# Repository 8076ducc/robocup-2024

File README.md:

# ducc. Robotics: RoboCupJunior Soccer 2024

This repository contains ducc's working files and source code for the 2024 RoboCupJunior Soccer Open and Soccer Lightweight competition.

## About

ducc is a six-man team comprising Neo Hao Jun, Isaac Tan, Zhu Yunsong, Aidan Yeong, Oliver Zhao, and Ng Aaron from the Hwa Chong Robotics Club in Singapore.

## Technologies

This project was built with the following tools:

- Mechanical: Autodesk Fusion 360
- Electrical: KiCad
- Programming: PlatformIO

## Intellectual Property

### Copyright

© 2023, ducc. Robotics Competition Team.

While we have made every effort to abide by legal and ethical requirements when using works that we did not create, some may have been overlooked inadvertently. Please let us know and we will be happy to make the necessary arrangements.

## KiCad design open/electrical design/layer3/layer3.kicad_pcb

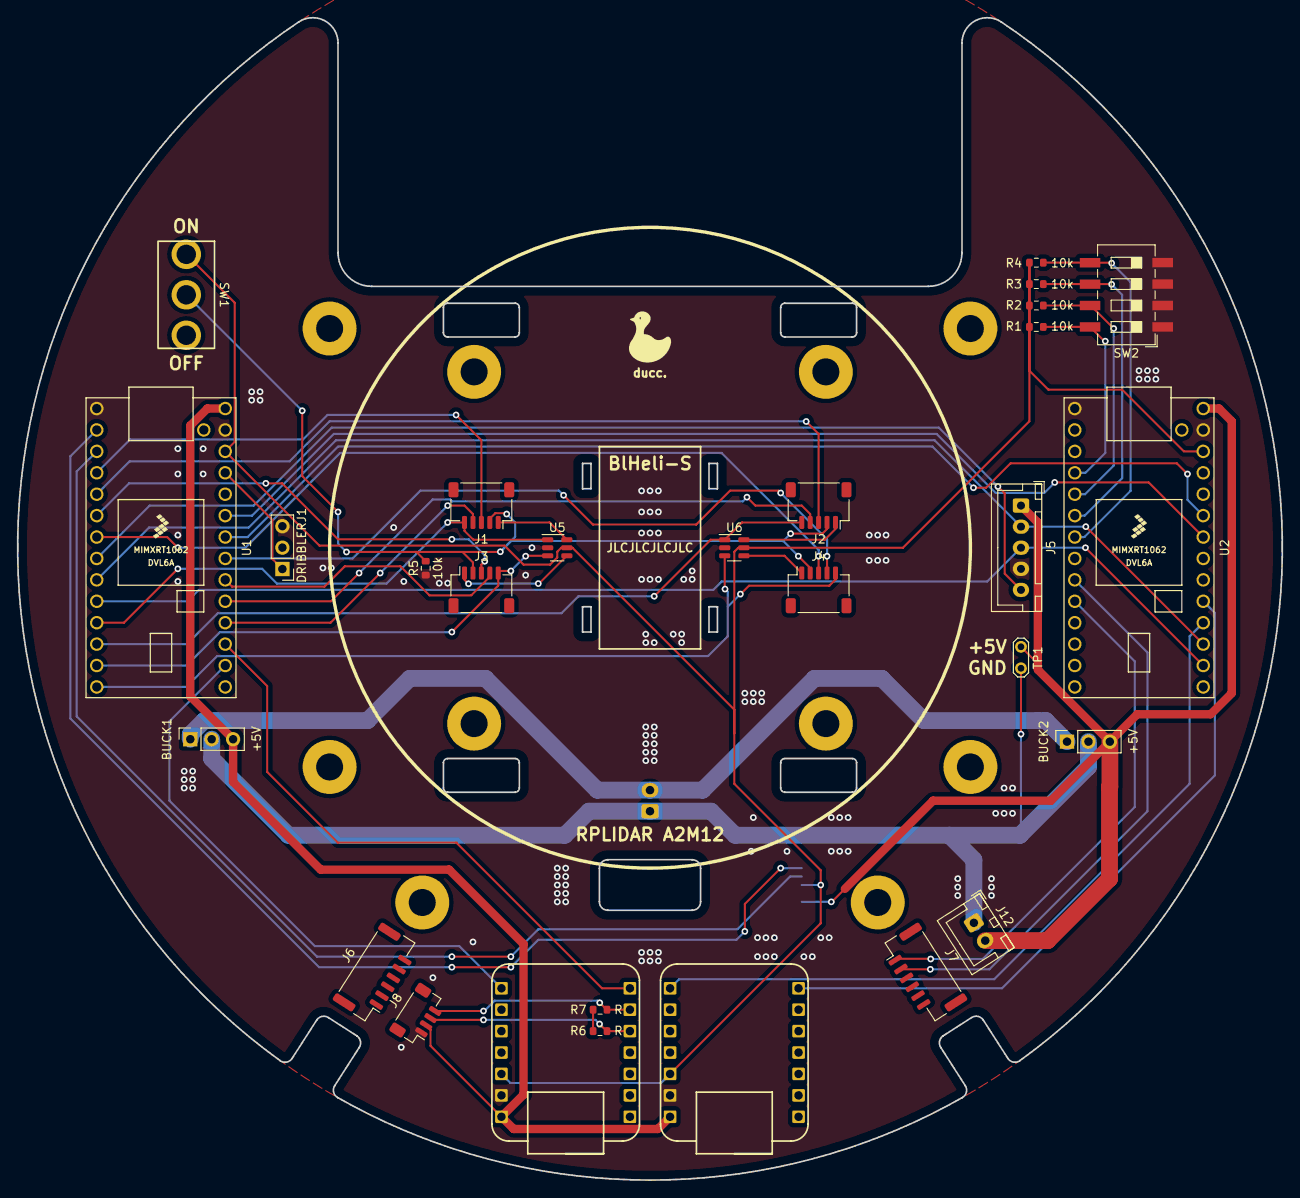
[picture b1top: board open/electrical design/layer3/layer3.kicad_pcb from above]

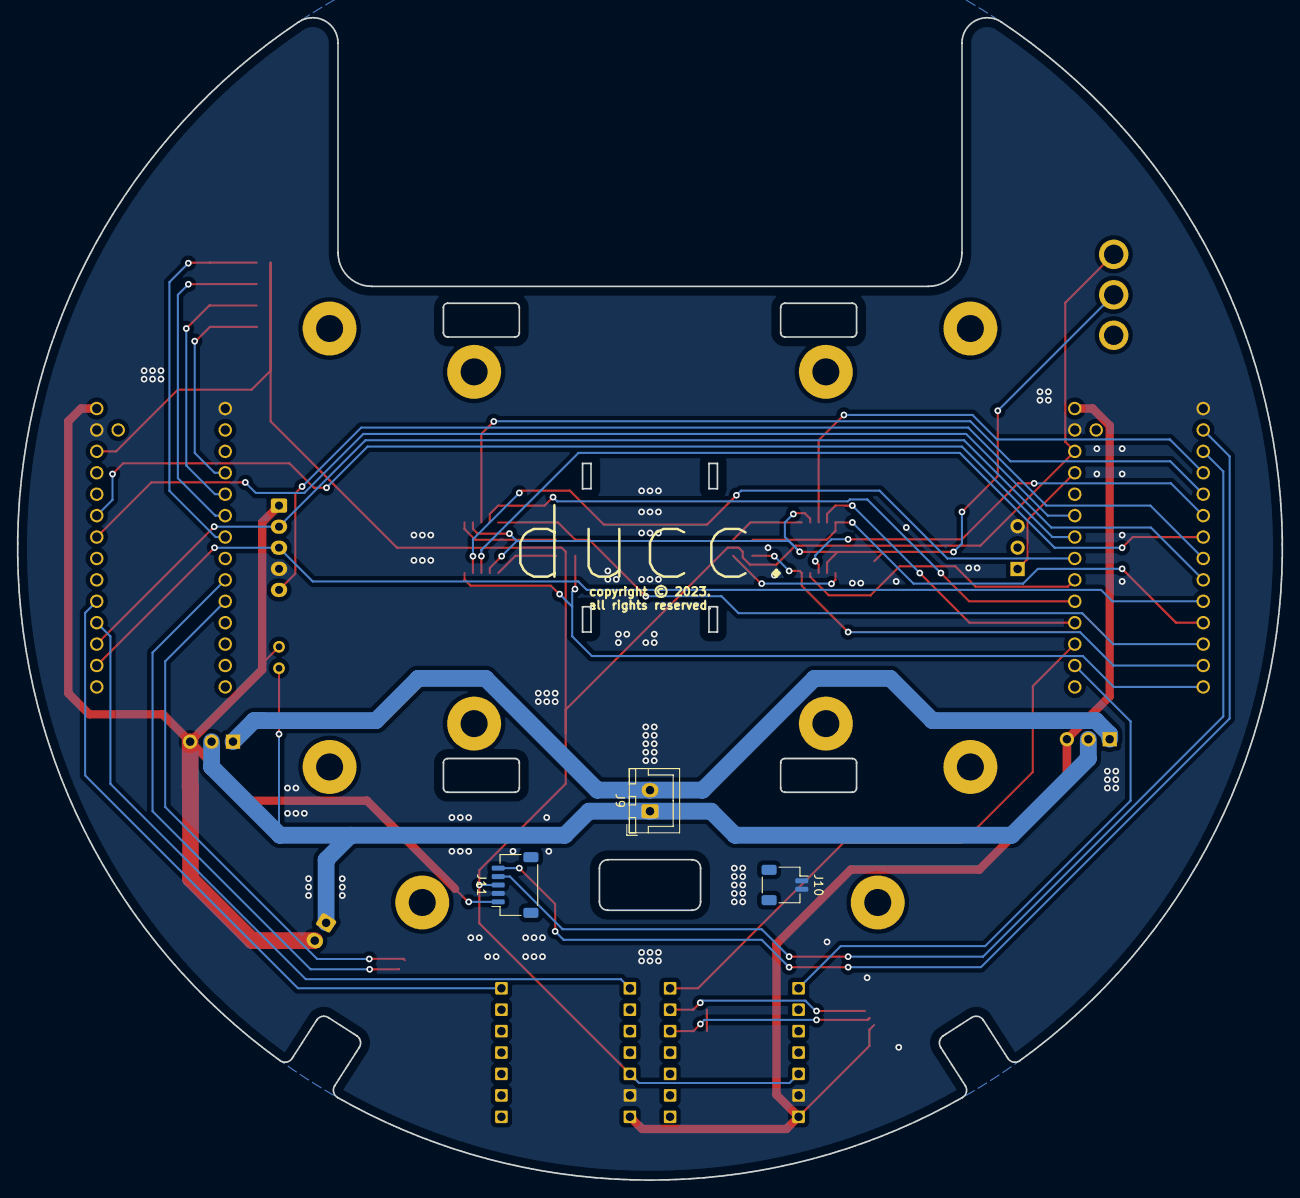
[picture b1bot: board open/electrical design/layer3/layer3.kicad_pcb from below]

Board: 2 copper layers, 150.0 x 137.9 mm, 41 parts (3 on the bottom side), 45 nets.

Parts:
BUCK1, BUCK2: +5V; TPS5430 Board
DRIBBLERJ1: Conn_01x03_Male; PinHeader_1x03_P2.54mm_Vertical
H1, H2, H3, H4, H5, H6, H7, H8, H9, H10: MountingHole; MountingHole_3.2mm_M3_Pad
J1, J2, J3, J4, J11: SH1.0 5P; JST_SH_SM05B-SRSS-TB_1x05-1MP_P1.00mm_Horizontal
J5: XH2.54 5P; JST_XH_B5B-XH-A_1x05_P2.50mm_Vertical
J6: CAMERA1; JST_GH_BM06B-GHS-TBT_1x06-1MP_P1.25mm_Vertical
J7: CAMERA2; JST_GH_BM06B-GHS-TBT_1x06-1MP_P1.25mm_Vertical
J8: COMPASS; JST_SH_BM04B-SRSS-TB_1x04-1MP_P1.00mm_Vertical
J9, J12: XH2.54 2P; JST_XH_B2B-XH-A_1x02_P2.50mm_Vertical
J10: SH1.0 2P; JST_SH_SM02B-SRSS-TB_1x02-1MP_P1.00mm_Horizontal
R1, R2, R3, R4, R5: 10k; R_0603_1608Metric
R6, R7: R; R_0603_1608Metric
SW1: SW_SPDT; SWITCH_SPDT_PTH_12.7X6.7MM
SW2: SW_DIP_x04; SW_DIP_SPSTx04_Slide_6.7x11.72mm_W8.61mm_P2.54mm_LowProfile
TP1: TestPoint_2Pole; TestPoint_2Pads_Pitch2.54mm_Drill0.8mm
U1, U2: TEENSY 4.0; Teensy40
U3, U4: MOUDLE-SEEEDUINO-XIAO-ESP32C3; xiao-esp32c3
U5, U6: 74LVC2G04; SOT-23-6

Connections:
+3V3: J11.3, R1.1, R2.1, R3.1, R4.1, SW1.1 (A), U1.3.3V_2, U2.3.3V_2, U3.12 (3V3), U4.12 (3V3), U5.5 (VCC), U6.5 (VCC)
+5V: BUCK1.3, BUCK2.3, J5.1, J8.2, J11.1, J12.2, TP1.1, U1.VIN, U2.VIN, U3.14 (5V), U4.14 (5V)
+12V: BUCK1.1, BUCK2.1, J9.2
/BTRX: U2.17, U4.7 (PB08_A6_D6_TX)
/BTTX: U2.16, U4.8 (PB09_A7_D7_RX)
/CAM1RX: J6.1, U2.1
/CAM1TX: J6.2, U2.0
/CAM2RX: J7.1, U2.8
/CAM2TX: J7.2, U2.7
/DRIBBLERPWM: DRIBBLERJ1.1, U1.23
/EN: J1.2, J2.2, J3.2, J4.2, R5.2, SW1.2 (B)
/IMURX: U1.14, U3.8 (PB09_A7_D7_RX)
/IMUSCL: J8.4, R7.1, U3.6 (PA9_A5_D5_SCL)
/IMUSDA: J8.3, R6.1, U3.5 (PA8_A4_D4_SDA)
/IMUTX: U1.15, U3.7 (PB08_A6_D6_TX)
/L1RX: J11.4, U1.1
/L1TX: J11.5, U1.0
/LIDARPWM: J5.5, U1.6
/LIDARRX: J5.3, U1.8, U2.14
/LIDARTX: J5.2, U1.7, U2.15
/M1CS: J1.4, U1.16
/M1INA: J1.5, U1.9, U5.1
/M1INB: J1.1, U5.6
/M1PWM: J1.3, U1.2
/M2CS: J2.4, U1.17
/M2INA: J2.5, U1.10, U6.1
/M2INB: J2.1, U6.6
/M2PWM: J2.3, U1.3
/M3CS: J3.4, U1.18
/M3INA: J3.5, U1.11, U5.3
/M3INB: J3.1, U5.4
/M3PWM: J3.3, U1.4
/M4CS: J4.4, U1.19
/M4INA: J4.5, U1.12, U6.3
/M4INB: J4.1, U6.4
/M4PWM: J4.3, U1.5
/RX: U1.20, U2.21
/STRAT1: R1.2, SW2.8, U2.2
/STRAT2: R2.2, SW2.7, U2.3
/STRAT3: R3.2, SW2.6, U2.4
/STRAT4: R4.2, SW2.5, U2.5
/TX: U1.21, U2.20
GNDD: DRIBBLERJ1.3, J5.4, J8.1, J10.1, J10.2, J11.2, R5.1, SW2.1, SW2.2, SW2.3, SW2.4, U1.G1, U1.G3, U2.G1, U2.G3, U3.13 (GND), U4.13 (GND), U5.2 (GND), U6.2 (GND)
GNDPWR: BUCK1.2, BUCK2.2, J9.1, J12.1, TP1.2
unnamed: R6.2, R7.2

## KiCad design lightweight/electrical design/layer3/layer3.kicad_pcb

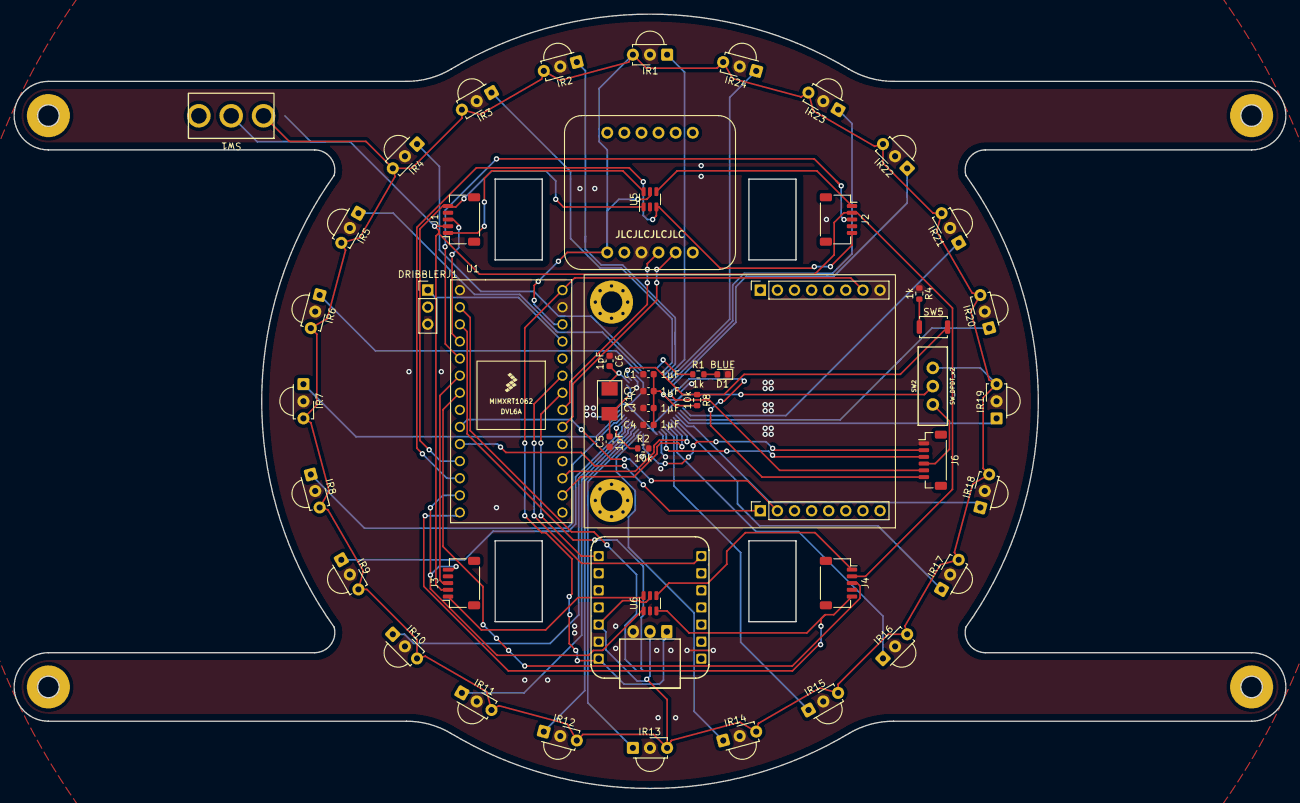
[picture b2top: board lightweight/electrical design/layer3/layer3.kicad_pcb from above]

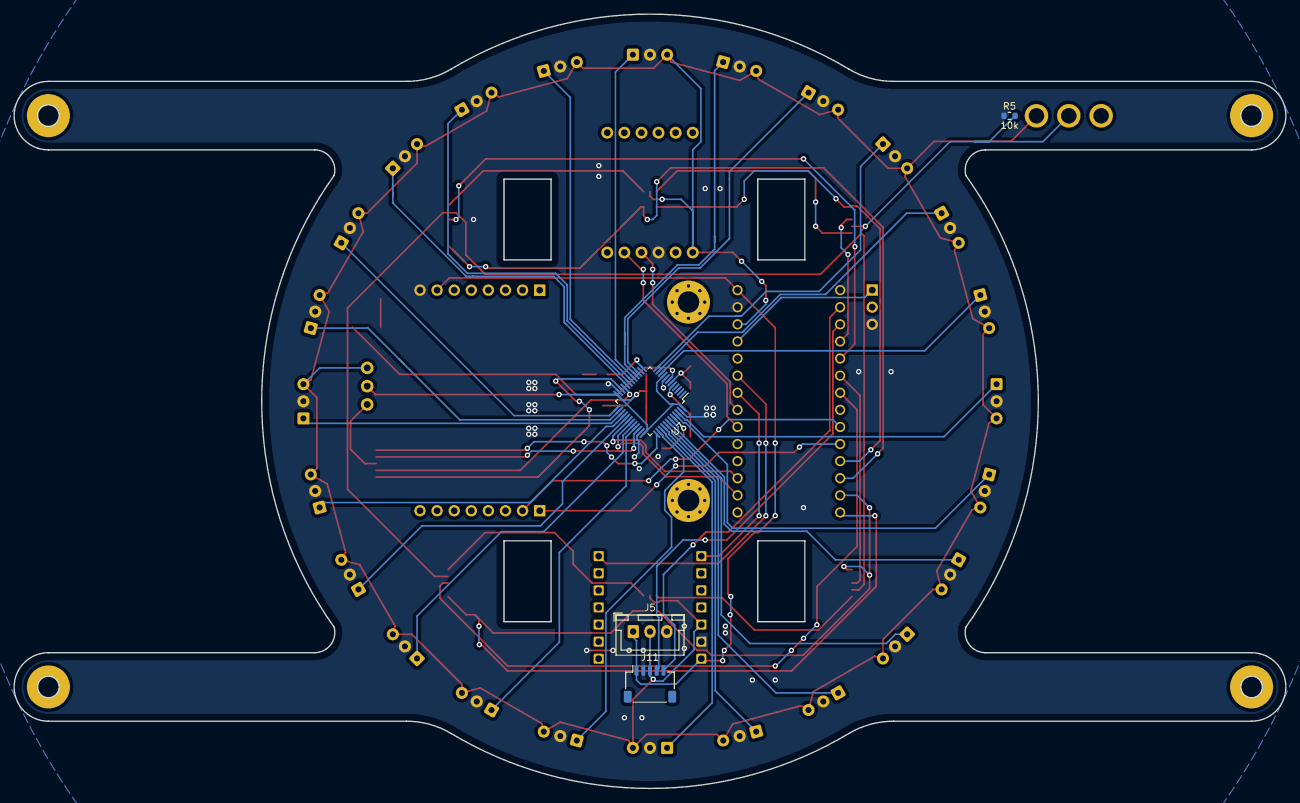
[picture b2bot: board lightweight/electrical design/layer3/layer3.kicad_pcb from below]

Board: 2 copper layers, 188.9 x 115.0 mm, 59 parts (4 on the bottom side), 64 nets.

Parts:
C1, C2, C3, C4: 1μF; C_0603_1608Metric
C5, C6: 1pF; C_0603_1608Metric
D1: BLUE; D_0603_1608Metric
DRIBBLERJ1: Conn_01x03_Male; PinHeader_1x03_P2.54mm_Vertical
H1, H2, H3, H4: MountingHole; MountingHole_3.2mm_M3_Pad
IR1, IR2, IR3, IR4, IR5, IR6, IR7, IR8, IR9, IR10, IR11, IR12, IR13, IR14, IR15, IR16, IR17, IR18, IR19, IR20, IR21, IR22, IR23, IR24: TSSP58038; Vishay_MINICAST-3Pin
J1, J2, J3, J4, J11: SH1.0 5P; JST_SH_SM05B-SRSS-TB_1x05-1MP_P1.00mm_Horizontal
J5: Conn_01x03_Pin; JST_XH_B3B-XH-A_1x03_P2.50mm_Vertical
J6: SH1.0 Female; JST_SH_BM06B-SRSS-TB_1x06-1MP_P1.00mm_Vertical
R1, R4: 1k; R_0603_1608Metric
R2, R5, R8: 10k; R_0603_1608Metric
SW1: SW_SPDT; SWITCH_SPDT_PTH_12.7X6.7MM
SW2: SW_DPDT_x2; SWITCH_SPDT_PTH_11.6X4.0MM_LOCK
SW5: SW_Push; SW_Push_SPST_NO_Alps_SKRK
U1: TEENSY 4.0; Teensy 4.0
U2: MOUDLE-SEEEDUINO-XIAO-ESP32C3; xiao-esp32c3
U3: Conn_01x16_Socket; openmv
U4: BNO085; bno085
U5, U6: 74LVC2G04; SOT-23-6
U7: STM32F103C8T6; LQFP-48_7x7mm_P0.5mm
Y1: Crystal; Crystal_SMD_5032-2Pin_5.0x3.2mm

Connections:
+3V3: IR1.3 (Vs), IR2.3 (Vs), IR3.3 (Vs), IR4.3 (Vs), IR5.3 (Vs), IR6.3 (Vs), IR7.3 (Vs), IR8.3 (Vs), IR9.3 (Vs), IR10.3 (Vs), IR11.3 (Vs), IR12.3 (Vs), IR13.3 (Vs), IR14.3 (Vs), IR15.3 (Vs), IR16.3 (Vs), IR17.3 (Vs), IR18.3 (Vs), IR19.3 (Vs), IR20.3 (Vs), IR21.3 (Vs), IR22.3 (Vs), IR23.3 (Vs), IR24.3 (Vs), J5.2, J11.3, SW1.1 (A), SW2.1 (A), U1.3.3V_2, U2.12 (3V3), U4.JP1_1 (VIN), U5.5 (VCC), U6.5 (VCC)
+5V: J5.1, J11.1, U1.VIN, U2.14 (5V), U3.10
/BTRX: U1.21, U2.7 (PB08_A6_D6_TX)
/BTTX: U1.20, U2.8 (PB09_A7_D7_RX)
/CAMRX: U1.8, U3.1
/CAMTX: U1.7, U3.2
/DRIBBLERPWM: DRIBBLERJ1.1, U1.23
/EN: J1.2, J2.2, J3.2, J4.2, R5.2, SW1.2 (B)
/IMUSCL: U1.19, U4.JP1_4 (SCL)
/IMUSDA: U1.18, U4.JP1_5 (SDA)
/L1RX: J11.4, U1.1
/L1TX: J11.5, U1.0
/M1INA: J1.5, U1.9, U5.1
/M1INB: J1.1, U5.6
/M1PWM: J1.3, U1.2
/M2INA: J2.5, U1.10, U5.3
/M2INB: J2.1, U5.4
/M2PWM: J2.3, U1.3
/M3INA: J3.5, U1.11, U6.1
/M3INB: J3.1, U6.6
/M3PWM: J3.3, U1.4
/M4INA: J4.5, U1.12, U6.3
/M4INB: J4.1, U6.4
/M4PWM: J4.3, U1.5
/ir/DEBUGRX: J6.6, U7.22 (PB11)
/ir/DEBUGTX: J6.5, U7.21 (PB10)
/ir/IR1: IR1.1 (OUT), U7.17 (PA7)
/ir/IR2: IR2.1 (OUT), U7.16 (PA6)
/ir/IR3: IR3.1 (OUT), U7.15 (PA5)
/ir/IR4: IR4.1 (OUT), U7.12 (PA2)
/ir/IR5: IR5.1 (OUT), U7.11 (PA1)
/ir/IR6: IR6.1 (OUT), U7.10 (PA0)
/ir/IR7: IR7.1 (OUT), U7.46 (PB9)
/ir/IR8: IR8.1 (OUT), U7.45 (PB8)
/ir/IR9: IR9.1 (OUT), U7.43 (PB7)
/ir/IR10: IR10.1 (OUT), U7.42 (PB6)
/ir/IR11: IR11.1 (OUT), U7.41 (PB5)
/ir/IR12: IR12.1 (OUT), U7.40 (PB4)
/ir/IR13: IR13.1 (OUT), U7.39 (PB3)
/ir/IR14: IR14.1 (OUT), U7.38 (PA15)
/ir/IR15: IR15.1 (OUT), U7.33 (PA12)
/ir/IR16: IR16.1 (OUT), U7.32 (PA11)
/ir/IR17: IR17.1 (OUT), U7.29 (PA8)
/ir/IR18: IR18.1 (OUT), U7.28 (PB15)
/ir/IR19: IR19.1 (OUT), U7.27 (PB14)
/ir/IR20: IR20.1 (OUT), U7.26 (PB13)
/ir/IR21: IR21.1 (OUT), U7.25 (PB12)
/ir/IR22: IR22.1 (OUT), U7.20 (PB2)
/ir/IR23: IR23.1 (OUT), U7.19 (PB1)
/ir/IR24: IR24.1 (OUT), U7.18 (PB0)
/ir/MCU3V3: C1.2, C2.2, C3.2, C4.2, R8.2, SW2.2 (B), U7.9 (VDDA), U7.24 (VDD), U7.36 (VDD), U7.48 (VDD)
/ir/OSCIN: C5.2, U7.5 (PD0), Y1.2
/ir/OSCOUT: C6.2, U7.6 (PD1), Y1.1
/ir/PROG3V3: J6.4, SW2.3 (C)
/ir/RESET: R8.1, SW5.2, U7.7 (NRST)
/ir/SWDCLOCK: J6.2, U7.37 (PA14)
/ir/SWDIO: J6.3, U7.34 (PA13)
GND: C1.1, C2.1, C3.1, C4.1, C5.1, C6.1, D1.1 (K), DRIBBLERJ1.3, IR1.2 (GND), IR2.2 (GND), IR3.2 (GND), IR4.2 (GND), IR5.2 (GND), IR6.2 (GND), IR7.2 (GND), IR8.2 (GND), IR9.2 (GND), IR10.2 (GND), IR11.2 (GND), IR12.2 (GND), IR13.2 (GND), IR14.2 (GND), IR15.2 (GND), IR16.2 (GND), IR17.2 (GND), IR18.2 (GND), IR19.2 (GND), IR20.2 (GND), IR21.2 (GND), IR22.2 (GND), IR23.2 (GND), IR24.2 (GND), J5.3, J6.1, J11.2, R2.2, R4.1, R5.1, U1.G1, U1.G3, U2.13 (GND), U3.9, U4.JP1_3 (GND), U5.2 (GND), U6.2 (GND), U7.8 (VSSA), U7.23 (VSS), U7.35 (VSS), U7.47 (VSS)
IRRX: U1.14, U7.31 (PA10)
IRTX: U1.15, U7.30 (PA9)
unnamed: D1.2 (A), R1.2
unnamed: R4.2, SW5.1
unnamed: R2.1, U7.44 (BOOT0)
unnamed: R1.1, U7.13 (PA3)

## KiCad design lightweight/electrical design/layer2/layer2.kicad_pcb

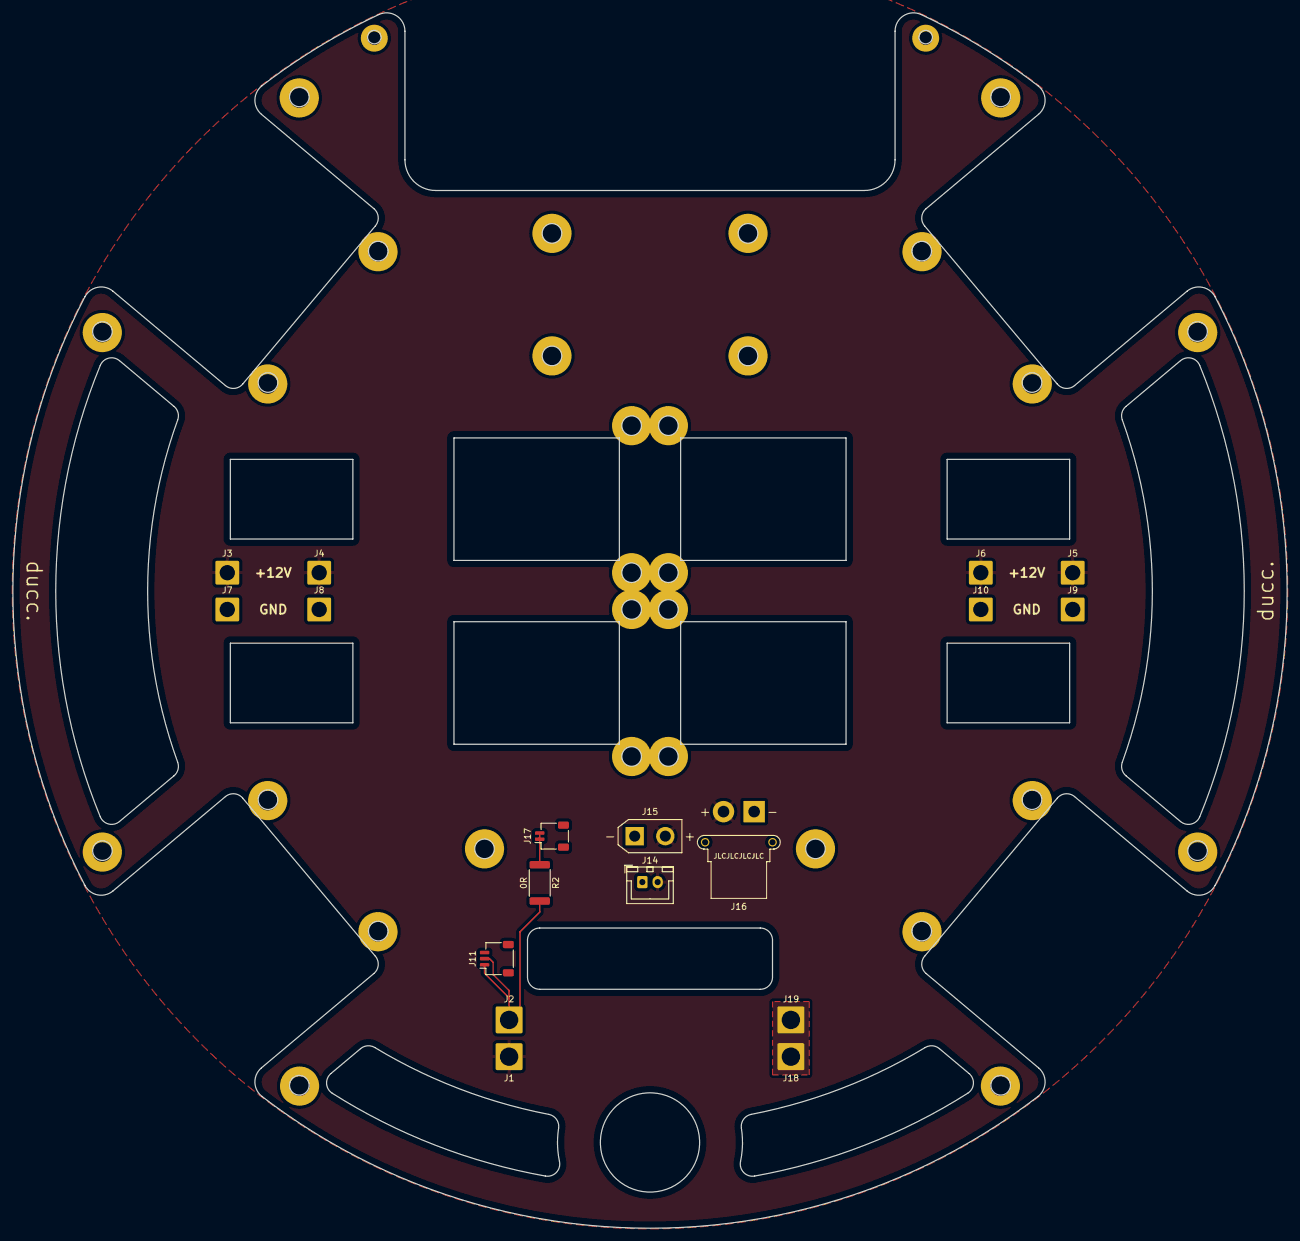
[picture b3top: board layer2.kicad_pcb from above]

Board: 2 copper layers, 208.0 x 198.4 mm, 50 parts (0 on the bottom side), 4 nets.

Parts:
H1, H2, H3, H4, H5, H6, H7, H8, H9, H10, H11, H12, H13, H14, H15, H16, H17, H18, H19, H20, H21, H22, H23, H24, H25, H26, H27, H28, H29, H30: MountingHole; MountingHole_3.2mm_M3_Pad
H33, H34: MountingHole; MountingHole_2.2mm_M2_Pad
J1, J2, J18, J19: Conn_01x01_Female; SolderWire-2.5sqmm_1x01_D2.4mm_OD4.4mm
J3, J4, J5, J6, J7, J8, J9, J10: Conn_01x01_Female; SolderWire-2sqmm_1x01_D2mm_OD3.9mm
J11: SH1.0 3P; JST_SH_SM03B-SRSS-TB_1x03-1MP_P1.00mm_Horizontal
J14: XH2.54 2P; JST_XH_B2B-XH-A_1x02_P2.50mm_Vertical
J15: XT30UPB-F; AMASS_XT30UPB-F_1x02_P5.0mm_Vertical
J16: XT30PW-F; AMASS_XT30PW-F_1x02_P2.50mm_Horizontal
J17: SH1.0 2P; JST_SH_SM02B-SRSS-TB_1x02-1MP_P1.00mm_Horizontal
R2: 0R; R_2512_6332Metric

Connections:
+12V: J1.1, J3.1, J4.1, J5.1, J6.1, J14.2, J15.2, J16.2
/BATT: J18.1, J19.1
GND: J2.1, J7.1, J8.1, J9.1, J10.1, J11.1, J11.2, J14.1, J15.1, J16.1, R2.2
unnamed: J17.1, J17.2, R2.1

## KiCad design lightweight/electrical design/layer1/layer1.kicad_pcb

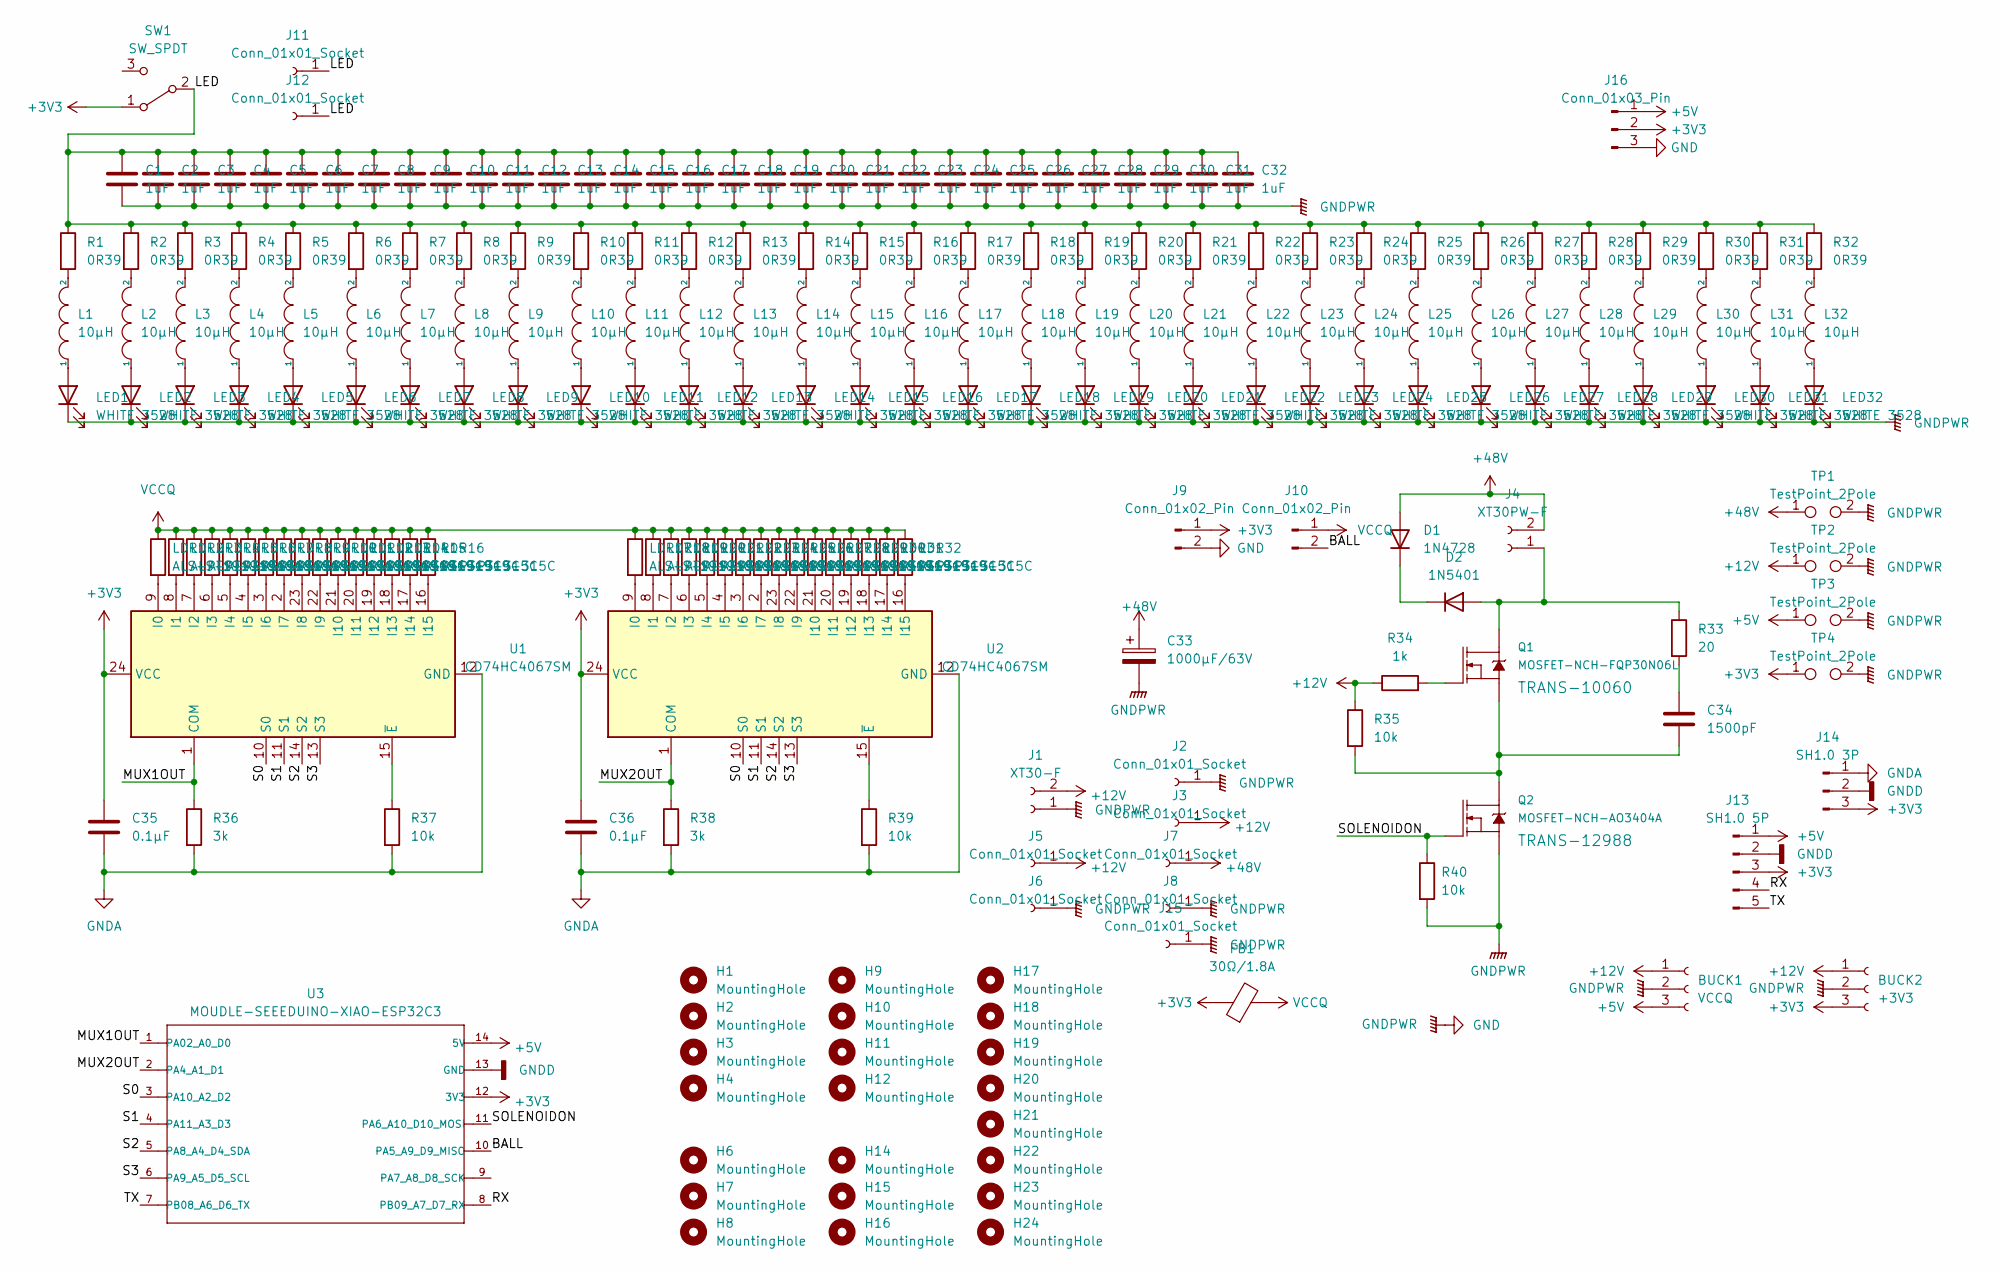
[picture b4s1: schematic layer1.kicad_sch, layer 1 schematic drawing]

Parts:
BUCK1: VCCQ; PinSocket_1x03_P2.54mm_Horizontal
BUCK2: +3V3; PinSocket_1x03_P2.54mm_Horizontal
C1, C2, C3, C4, C5, C6, C7, C8, C9, C10, C11, C12, C13, C14, C15, C16, C17, C18, C19, C20, C21, C22, C23, C24, C25, C26, C27, C28, C29, C30, C31, C32: 1uF; C_0603_1608Metric
C33: 1000µF/63V; CP_Radial_D16.0mm_P7.50mm
C34: 1500pF; C_0603_1608Metric
C35, C36: 0.1μF; C_0603_1608Metric
D1: 1N4728; D_DO-41_SOD81_P10.16mm_Horizontal
D2: 1N5401; D_DO-27_P15.24mm_Horizontal
FB1: 30Ω/1.8A; C_0603_1608Metric
H1, H2, H3, H4, H6, H7, H8, H9, H10, H11, H12, H14, H15, H16, H17, H18, H19, H20, H21, H22, H23, H24: MountingHole; MountingHole_3.2mm_M3_Pad
J1: XT30-F; AMASS_XT30UPB-F_1x02_P5.0mm_Vertical
J2, J11, J15: Conn_01x01_Socket; SolderWirePad_1x01_SMD_1x2mm
J3, J5, J6, J7, J8: Conn_01x01_Socket; SolderWirePad_1x01_SMD_5x10mm
J4: XT30PW-F; AMASS_XT30UPB-F_1x02_P5.0mm_Vertical
J9, J10: Conn_01x02_Pin; PinHeader_1x02_P2.54mm_Vertical
J12: Conn_01x01_Socket; SolderWire-0.5sqmm_1x01_D0.9mm_OD2.1mm
J13: SH1.0 5P; JST_SH_BM05B-SRSS-TB_1x05-1MP_P1.00mm_Vertical
J14: SH1.0 3P; JST_SH_BM03B-SRSS-TB_1x03-1MP_P1.00mm_Vertical
J16: Conn_01x03_Pin; JST_XH_B3B-XH-A_1x03_P2.50mm_Vertical
L1, L2, L3, L4, L5, L6, L7, L8, L9, L10, L11, L12, L13, L14, L15, L16, L17, L18, L19, L20, L21, L22, L23, L24, L25, L26, L27, L28, L29, L30, L31, L32: 10µH; L_0805_2012Metric
LDR1, LDR2, LDR3, LDR4, LDR5, LDR6, LDR7, LDR8, LDR9, LDR10, LDR11, LDR12, LDR13, LDR14, LDR15, LDR16, LDR17, LDR18, LDR19, LDR20, LDR21, LDR22, LDR23, LDR24, LDR25, LDR26, LDR27, LDR28, LDR29, LDR30, LDR31, LDR32: ALS-PT19-315C; D_0603_1608Metric
LED1, LED2, LED3, LED4, LED5, LED6, LED7, LED8, LED9, LED10, LED11, LED12, LED13, LED14, LED15, LED16, LED17, LED18, LED19, LED20, LED21, LED22, LED23, LED24, LED25, LED26, LED27, LED28, LED29, LED30, LED31, LED32: WHITE 3528; CP_EIA-3528-12_Kemet-T
Q1: MOSFET-NCH-FQP30N06L; TO-220-3_Vertical
Q2: MOSFET-NCH-AO3404A; TSOT-23
R1, R2, R3, R4, R5, R6, R7, R8, R9, R10, R11, R12, R13, R14, R15, R16, R17, R18, R19, R20, R21, R22, R23, R24, R25, R26, R27, R28, R29, R30, R31, R32: 0R39; R_0603_1608Metric
R33: 20; R_0603_1608Metric
R34: 1k; R_0603_1608Metric
R35, R37, R39, R40: 10k; R_0603_1608Metric
R36, R38: 3k; R_0603_1608Metric
SW1: SW_SPDT; SWITCH_SPDT_PTH_11.6X4.0MM
TP1, TP2, TP3, TP4: TestPoint_2Pole; TestPoint_2Pads_Pitch2.54mm_Drill0.8mm
U1, U2: CD74HC4067SM; SOIC-24W_7.5x15.4mm_P1.27mm
U3: MOUDLE-SEEEDUINO-XIAO-ESP32C3; xiao-esp32c3

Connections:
+3V3: BUCK2.3, C35.1, C36.1, FB1.1, J9.1, J13.3, J14.3, J16.2, SW1.1 (A), TP4.1, U1.24 (VCC), U2.24 (VCC), U3.12 (3V3)
+5V: BUCK1.3, J13.1, J16.1, TP3.1, U3.14 (5V)
+12V: BUCK1.1, BUCK2.1, J1.2, J3.1, J5.1, R34.1, R35.1, TP2.1
+48V: C33.1, D1.2 (A), J4.2, J7.1, TP1.1
/BALL: J10.2, U3.10 (PA5_A9_D9_MISO)
/LED: C1.1, C2.1, C3.1, C4.1, C5.1, C6.1, C7.1, C8.1, C9.1, C10.1, C11.1, C12.1, C13.1, C14.1, C15.1, C16.1, C17.1, C18.1, C19.1, C20.1, C21.1, C22.1, C23.1, C24.1, C25.1, C26.1, C27.1, C28.1, C29.1, C30.1, C31.1, C32.1, J11.1, J12.1, R1.1, R2.1, R3.1, R4.1, R5.1, R6.1, R7.1, R8.1, R9.1, R10.1, R11.1, R12.1, R13.1, R14.1, R15.1, R16.1, R17.1, R18.1, R19.1, R20.1, R21.1, R22.1, R23.1, R24.1, R25.1, R26.1, R27.1, R28.1, R29.1, R30.1, R31.1, R32.1, SW1.2 (B)
/MUX1OUT: R36.1, U1.1 (COM), U3.1 (PA02_A0_D0)
/MUX2OUT: R38.1, U2.1 (COM), U3.2 (PA4_A1_D1)
/RX: J13.4, U3.8 (PB09_A7_D7_RX)
/S0: U1.10 (S0), U2.10 (S0), U3.3 (PA10_A2_D2)
/S1: U1.11 (S1), U2.11 (S1), U3.4 (PA11_A3_D3)
/S2: U1.14 (S2), U2.14 (S2), U3.5 (PA8_A4_D4_SDA)
/S3: U1.13 (S3), U2.13 (S3), U3.6 (PA9_A5_D5_SCL)
/SOLENOIDON: Q2.1 (G), R40.1, U3.11 (PA6_A10_D10_MOSI)
/TX: J13.5, U3.7 (PB08_A6_D6_TX)
GND: BUCK1.2, BUCK2.2, C1.2, C2.2, C3.2, C4.2, C5.2, C6.2, C7.2, C8.2, C9.2, C10.2, C11.2, C12.2, C13.2, C14.2, C15.2, C16.2, C17.2, C18.2, C19.2, C20.2, C21.2, C22.2, C23.2, C24.2, C25.2, C26.2, C27.2, C28.2, C29.2, C30.2, C31.2, C32.2, C33.2, J1.1, J2.1, J6.1, J8.1, J9.2, J15.1, J16.3, LED1.1 (K), LED2.1 (K), LED3.1 (K), LED4.1 (K), LED5.1 (K), LED6.1 (K), LED7.1 (K), LED8.1 (K), LED9.1 (K), LED10.1 (K), LED11.1 (K), LED12.1 (K), LED13.1 (K), LED14.1 (K), LED15.1 (K), LED16.1 (K), LED17.1 (K), LED18.1 (K), LED19.1 (K), LED20.1 (K), LED21.1 (K), LED22.1 (K), LED23.1 (K), LED24.1 (K), LED25.1 (K), LED26.1 (K), LED27.1 (K), LED28.1 (K), LED29.1 (K), LED30.1 (K), LED31.1 (K), LED32.1 (K), Q2.2 (S), R40.2, TP1.2, TP2.2, TP3.2, TP4.2
GNDA: C35.2, C36.2, J14.1, R36.2, R37.2, R38.2, R39.2, U1.12 (GND), U2.12 (GND)
GNDD: J13.2, J14.2, U3.13 (GND)
unnamed: C34.1, R33.2
unnamed: D1.1 (K), D2.1 (K)
unnamed: D2.2 (A), J4.1, Q1.2 (D), R33.1
unnamed: L1.2, R1.2
unnamed: L2.2, R2.2
unnamed: L3.2, R3.2
unnamed: L4.2, R4.2
unnamed: L5.2, R5.2
unnamed: L6.2, R6.2
unnamed: L7.2, R7.2
unnamed: L8.2, R8.2
unnamed: L9.2, R9.2
unnamed: L10.2, R10.2
unnamed: L11.2, R11.2
unnamed: L12.2, R12.2
unnamed: L13.2, R13.2
unnamed: L14.2, R14.2
unnamed: L15.2, R15.2
unnamed: L16.2, R16.2
unnamed: L17.2, R17.2
unnamed: L18.2, R18.2
unnamed: L19.2, R19.2
unnamed: L20.2, R20.2
unnamed: L21.2, R21.2
unnamed: L22.2, R22.2
unnamed: L23.2, R23.2
unnamed: L24.2, R24.2
unnamed: L25.2, R25.2
unnamed: L26.2, R26.2
unnamed: L27.2, R27.2
unnamed: L28.2, R28.2
unnamed: L29.2, R29.2
unnamed: L30.2, R30.2
unnamed: L31.2, R31.2
unnamed: L32.2, R32.2
unnamed: L1.1, LED1.2 (A)
unnamed: L2.1, LED2.2 (A)
unnamed: L3.1, LED3.2 (A)
unnamed: L4.1, LED4.2 (A)
unnamed: L5.1, LED5.2 (A)
unnamed: L6.1, LED6.2 (A)
unnamed: L7.1, LED7.2 (A)
unnamed: L8.1, LED8.2 (A)
unnamed: L9.1, LED9.2 (A)
unnamed: L10.1, LED10.2 (A)
unnamed: L11.1, LED11.2 (A)
unnamed: L12.1, LED12.2 (A)
unnamed: L13.1, LED13.2 (A)
unnamed: L14.1, LED14.2 (A)
unnamed: L15.1, LED15.2 (A)
unnamed: L16.1, LED16.2 (A)
unnamed: L17.1, LED17.2 (A)
unnamed: L18.1, LED18.2 (A)
unnamed: L19.1, LED19.2 (A)
unnamed: L20.1, LED20.2 (A)
unnamed: L21.1, LED21.2 (A)
unnamed: L22.1, LED22.2 (A)
unnamed: L23.1, LED23.2 (A)
unnamed: L24.1, LED24.2 (A)
unnamed: L25.1, LED25.2 (A)
unnamed: L26.1, LED26.2 (A)
unnamed: L27.1, LED27.2 (A)
unnamed: L28.1, LED28.2 (A)
unnamed: L29.1, LED29.2 (A)
unnamed: L30.1, LED30.2 (A)
unnamed: L31.1, LED31.2 (A)
unnamed: L32.1, LED32.2 (A)
unnamed: Q1.1 (G), R34.2
unnamed: C34.2, Q1.3 (S), Q2.3 (D), R35.2
unnamed: LDR1.2, U1.9 (I0)
unnamed: LDR2.2, U1.8 (I1)
unnamed: LDR3.2, U1.7 (I2)
unnamed: LDR4.2, U1.6 (I3)
unnamed: LDR5.2, U1.5 (I4)
unnamed: LDR6.2, U1.4 (I5)
unnamed: LDR7.2, U1.3 (I6)
unnamed: LDR8.2, U1.2 (I7)
unnamed: LDR9.2, U1.23 (I8)
unnamed: LDR10.2, U1.22 (I9)
unnamed: LDR11.2, U1.21 (I10)
unnamed: LDR12.2, U1.20 (I11)
unnamed: LDR13.2, U1.19 (I12)
unnamed: LDR14.2, U1.18 (I13)
unnamed: LDR15.2, U1.17 (I14)
unnamed: LDR16.2, U1.16 (I15)
unnamed: R37.1, U1.15 (~E)
unnamed: LDR17.2, U2.9 (I0)
unnamed: LDR18.2, U2.8 (I1)
unnamed: LDR19.2, U2.7 (I2)
unnamed: LDR20.2, U2.6 (I3)
unnamed: LDR21.2, U2.5 (I4)
unnamed: LDR22.2, U2.4 (I5)
unnamed: LDR23.2, U2.3 (I6)
unnamed: LDR24.2, U2.2 (I7)
unnamed: LDR25.2, U2.23 (I8)
unnamed: LDR26.2, U2.22 (I9)
unnamed: LDR27.2, U2.21 (I10)
unnamed: LDR28.2, U2.20 (I11)
unnamed: LDR29.2, U2.19 (I12)
unnamed: LDR30.2, U2.18 (I13)
unnamed: LDR31.2, U2.17 (I14)
unnamed: LDR32.2, U2.16 (I15)
unnamed: R39.1, U2.15 (~E)
VCCQ: FB1.2, J10.1, LDR1.1, LDR2.1, LDR3.1, LDR4.1, LDR5.1, LDR6.1, LDR7.1, LDR8.1, LDR9.1, LDR10.1, LDR11.1, LDR12.1, LDR13.1, LDR14.1, LDR15.1, LDR16.1, LDR17.1, LDR18.1, LDR19.1, LDR20.1, LDR21.1, LDR22.1, LDR23.1, LDR24.1, LDR25.1, LDR26.1, LDR27.1, LDR28.1, LDR29.1, LDR30.1, LDR31.1, LDR32.1

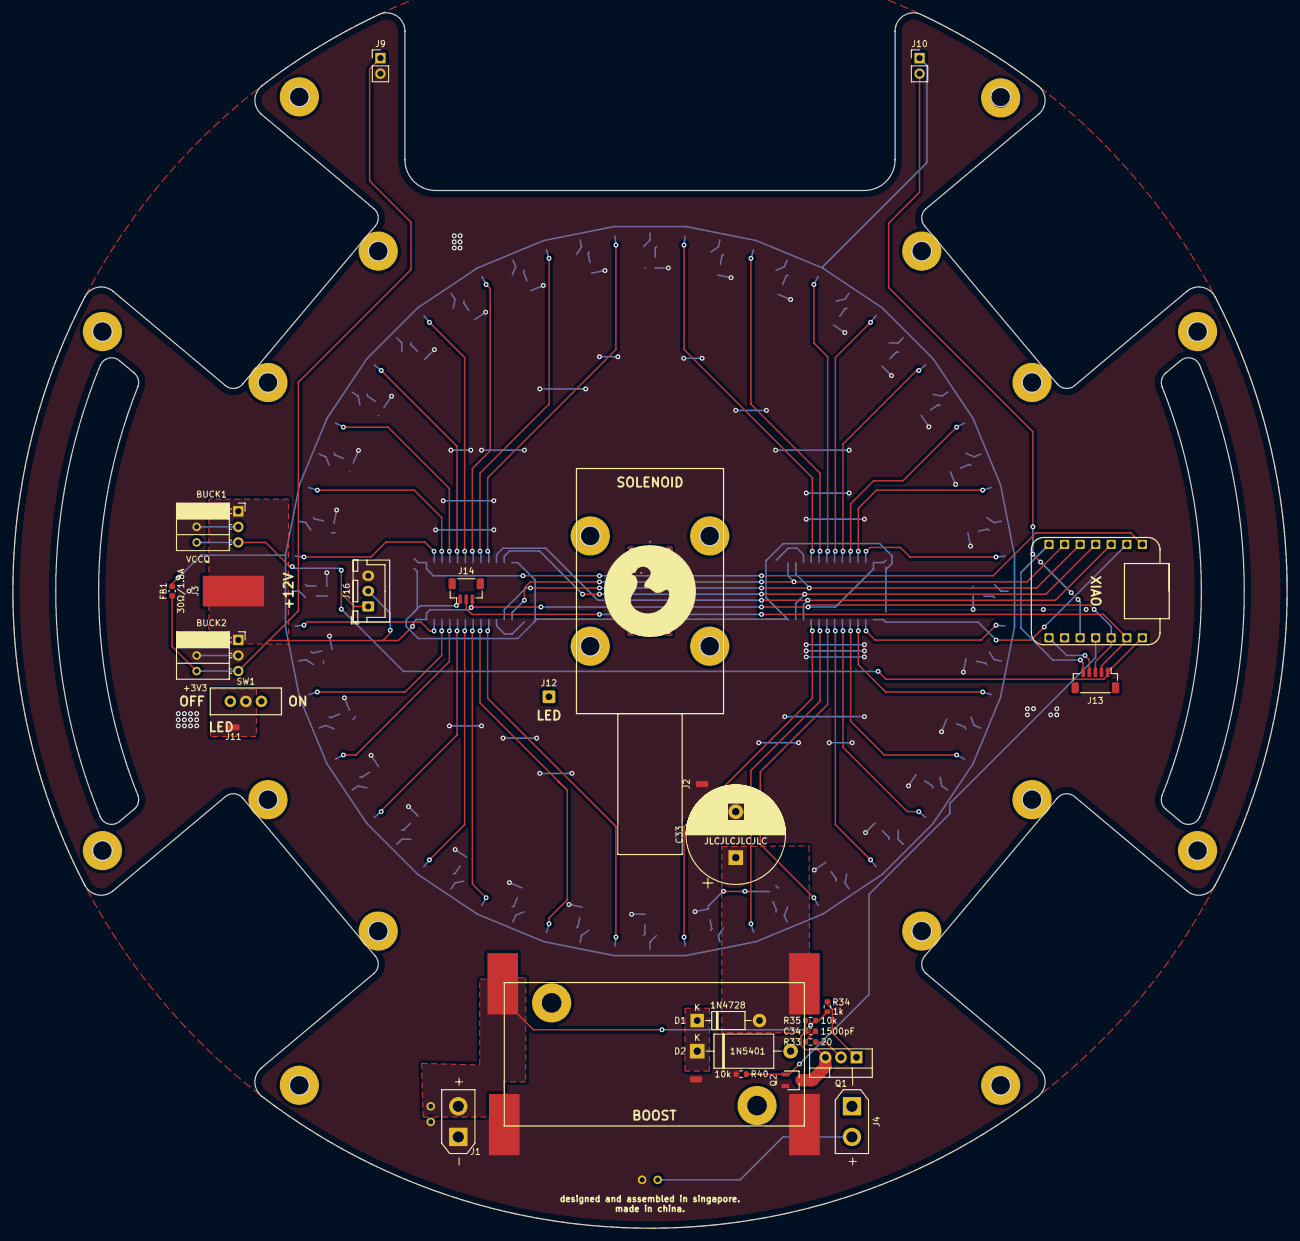
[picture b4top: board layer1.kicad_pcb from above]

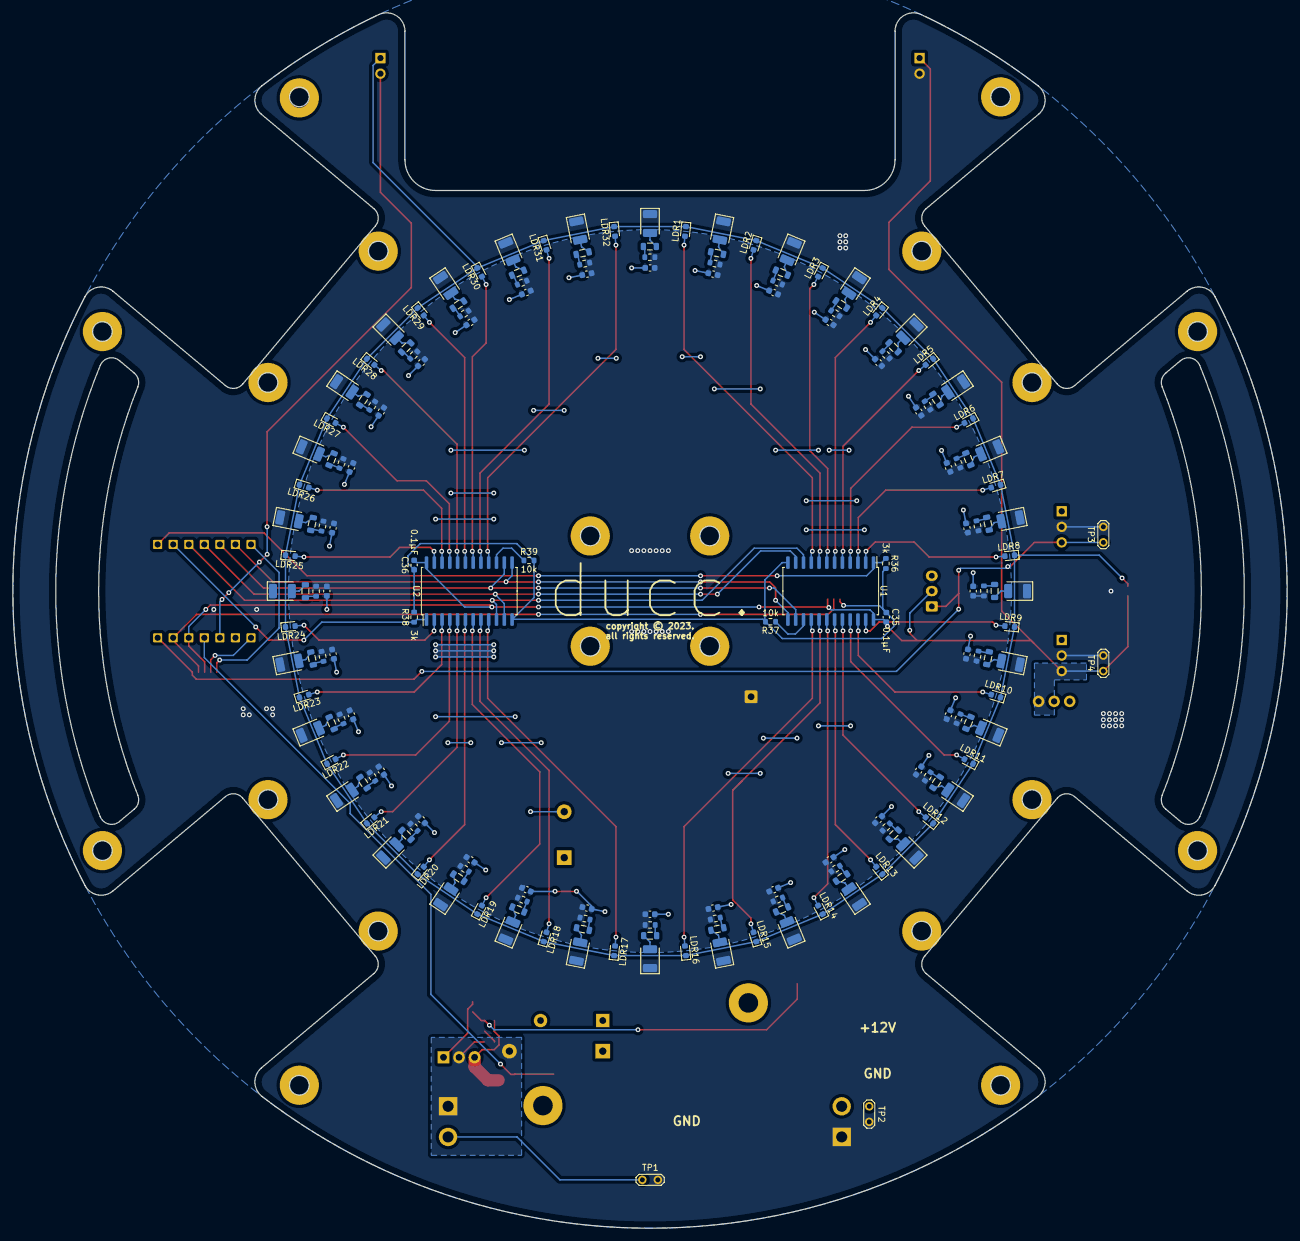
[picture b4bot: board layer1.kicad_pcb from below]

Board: 2 copper layers, 208.0 x 198.4 mm, 225 parts (172 on the bottom side), 122 nets.

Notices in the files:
lightweight/electrical design/layer1/layer1.kicad_pcb:
all rights reserved.
